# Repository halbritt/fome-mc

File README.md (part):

# `fome-mc` — Integrated FOME-Native Motorcycle ECU

**`fome-mc`** is a single-PCB, 4-layer (`162.0 mm × 115.0 mm`), pottable motorcycle engine control unit running [FOME (`fome-fw`)](https://github.com/halbritt/fome-fw) on an `STM32H753ZIT6` / `STM32H743ZIT6` paired with **two onboard `STM32F042K6T6` Bosch LSU 4.9 wideband controllers**, **four 400 V / 30 A ignition IGBTs**, **four 5 V logic ignition outputs**, **four high-Z injector drivers**, **dual 4-wire stepper drivers (`DRV8825` + `2× TLE9201SG`)**, **dual `MAX9924` adaptive VR conditioners**, **soldered 4 GB industrial SDNAND logging (`CSNP32GCR01-AOW`)**, **onboard `ATWINC1500-MR210UB` U.FL Wi-Fi**, and **dual 35-pin TE Connectivity AMPSEAL (`776163-1` Black & `776163-2` Grey) sealed harness headers**.

The primary reference application is the **2007 Suzuki SV650 (K7)** (`645 cc` 90° V-twin, odd-fire `270° / 450°`, dual spark plugs per cylinder = 4 plugs total, `24-2` crank VR trigger, camless `VVT_MAP_V_TWIN` intake-MAP phase sync, dual 4-wire steppers for `ISC` idle and `STVA` secondary throttle blades, and dual Bosch LSU 4.9 wideband O2 sensors).

---

## Documentation & Visual Index

| Document / Artifact | Description |
| :--- | :--- |
| [**`docs/WIRING_SV650_K7.md`**](docs/WIRING_SV650_K7.md) | Complete 2007 Suzuki SV650 (K7) adapter harness build guide, stock 2×34-pin ECM cavity key, mating TE AMPSEAL connector BOM, pin-by-pin `J1`/`J2` cross-reference, 2-coil vs. 4-coil Primary+Trailing ignition wiring, and dual Bosch LSU 4.9 pinouts |
| [**`docs/POTTING_AND_ENCLOSURE.md`**](docs/POTTING_AND_ENCLOSURE.md) | CNC enclosure stackup, faceplate/bulkhead cutouts, `10.44 W` continuous / `12.74 W` peak thermal dissipation budget, thermal gap-pad coupling, single-pour flood potting (external GM/Delphi 1-bar baro, `FOMEMC-1`), `U29` U.FL RF shield sealing (`FOMEMC-2`), and post-potting DFU recovery |
| [**`docs/TELEMETRY_AND_RACECHRONO.md`**](docs/TELEMETRY_AND_RACECHRONO.md) | `CAN1` motorsport telemetry pod (`ESP32-S3` + `25 Hz` GPS + `Bosch MM5.10` / `BMI088` 6-axis IMU + brake/suspension ADC), `FOME_CAN_verbose.dbc` (`0x200..0x207` @ 50 Hz), RaceChrono Pro BLE DIY integration, and Insta360 / DJI Action camera sync (`FOMEMC-4`) |
| [**`docs/DESIGN.md`**](docs/DESIGN.md) | Complete electrical architecture, circuit-block reuse/adaptation ledger, power tree, and STM32H753 resource mapping |
| [**`docs/VALIDATION.md`**](docs/VALIDATION.md) | Automated ERC/DRC/Parity/Gerber/JLCPCB DFM verification ledger and pre-engine hardware bring-up checklist |
| [**`docs/SHEET_CONTRACTS.md`**](docs/SHEET_CONTRACTS.md) | Per-sheet hierarchical pin contracts (`contracts/*.interface.json`, `633` invariants across 15 sheets / 21 instances) and cross-block coupling resolution (`FOMEMC-22`) |
| [**`docs/BLOCK_LIBRARY.md`**](docs/BLOCK_LIBRARY.md) | Reference circuit-block library capture plan and provenance inventory across `fome-mc` subsheets |
| [**`docs/SEEDED_DEFECT_BENCHMARK.md`**](docs/SEEDED_DEFECT_BENCHMARK.md) | Seeded hardware defect benchmark catalog derived from `FOMEMC-1..27` design and layout remediations |
| [**`toolchain/README.md`**](toolchain/README.md) & [**`toolchain/ROUTING.md`**](toolchain/ROUTING.md) | Reproducible KiCad 10 / `kicad-happy` / `ngspice` check runner and `kicad-route` PCB routing workflow |
| [**`docs/schematics/fome-mc-schematics.pdf`**](docs/schematics/fome-mc-schematics.pdf) | Full 21-sheet hierarchical schematic PDF (plus individual sheet SVGs in [`docs/schematics/`](docs/schematics/)) |
| [**`docs/renders/fome-mc-pcb-layers.pdf`**](docs/renders/fome-mc-pcb-layers.pdf) | Multi-page PCB layer plot PDF (`F.Cu`, `In1.Cu`, `In2.Cu`, `B.Cu`, `F.Silkscreen`, `B.Silkscreen`, `F.Fab`, `Edge.Cuts`) |
| [**3D board renderings**](docs/renders/3d/fome-mc-3d-isometric.png) | High-resolution [top](docs/renders/3d/fome-mc-3d-top.png), [bottom](docs/renders/3d/fome-mc-3d-bottom.png) and [isometric](docs/renders/3d/fome-mc-3d-isometric.png) views, with [source and model provenance](docs/renders/3d/render-manifest.json) |
| [**`io-map.csv`**](io-map.csv) | Machine-verified 92-row master pinout CSV (`J1-1..35`, `J2-1..35`, and 22 internal MCU/WBO/SDNAND/Wi-Fi/power buses) |
| [**`export/BOM-fome-mc.csv`**](export/BOM-fome-mc.csv), [**`export/CPL-fome-mc.csv`**](export/CPL-fome-mc.csv) & [**`fab-manifest.json`**](reports/toolchain/fab-manifest.json) | JLCPCB PCBA Bill of Materials (`494` populated parts across `102` lines), component placement centroids, and SHA-256 fabrication package manifest (`FOMEMC-21`, `FOMEMC-24`) |
| [**`CHANGELOG.md`**](CHANGELOG.md) | Engineering decision history, schematic/PCB integration milestones, and upstream bug fixes |

---

## System Architecture

```mermaid
flowchart TB
    subgraph J1["J1 — TE AMPSEAL 35-Pin (Black 776163-1): Power & High-Current Outputs"]
        J1_PWR["+12V_IGN_SW (J1-26)<br/>+12V_MR (J1-24, J1-27)<br/>Perm_Live (J1-28)<br/>WBO1/2_H- (J1-23, J1-25)"]
        J1_INJ["INJ1..INJ4 (J1-1..4)<br/>4x High-Z Injector LS"]
        J1_IGBT["IGBT1..IGBT4 (J1-6..9)<br/>4x 400V 30A Dumb Coil IGBTs"]
        J1_AUX["AUX_LS1..4 (J1-10..13)<br/>Fuel Pump, Fan, PAIR, Tach<br/>MAIN_RLY LS (J1-14)"]
        J1_MOT["ETB1+/- & ETB2+/- (J1-15..18)<br/>STEP_1A/1B/2A/2B (J1-19..22)"]
        J1_DFU["USB_VBUS / +12V DFU (J1-35)<br/>5V_SENSOR_1/2 (J1-29..30)<br/>Unified GND (J1-5, J1-31..34)"]
    end

    subgraph J2["J2 — TE AMPSEAL 35-Pin (Grey 776163-2): Sensors, Wideband Cells & Comms"]
        J2_ANA["CLT, IAT, TPS1, TPS2_STPS,<br/>MAP1_FRONT, AV3_BARO_MAP2,<br/>AV5_TIPOVER, AV6_GEAR (J2-1..8)"]
        J2_KNK["KNOCK1 & KNOCK2 (J2-9..10)"]
        J2_TRG["VR1+/- & VR2+/- (J2-11..14)<br/>HALL1..3 & DIN1 (J2-15..18)"]
        J2_WBO["WBO1 LSU 4.9 (J2-19..22)<br/>WBO2 LSU 4.9 (J2-30..33)"]
        J2_IGN["IGN1_LOG..IGN4_LOG (J2-23..26)<br/>DASH_TECH 7800-Baud (J2-27)"]
        J2_COM["CAN1_H/L (J2-28..29, 500 kbps)<br/>USB_D+/D- (J2-34..35)"]
    end

    subgraph PCB["fome-mc 4-Layer Integrated Motorcycle ECU PCB (162.0 mm × 115.0 mm)"]
        PSU["Power Supply & Keep-Alive (psu.kicad_sch + Keep_Alive.kicad_sch)<br/>D20/D21 B340A Diode-OR (12V_IGN_SW + 12V_MR -> 12V_RAW)<br/>SMCJ24A (D1/D22) Unidirectional TVS • AO4485 Reverse PMOS + BZT52C12<br/>L1/C6 Input Filter -> LMR16020PDDAR 60V 5V Buck • 2x TLS115D0E<br/>TLV75733PDBVR 3.3V LDO • MIC5205 VBAT (U41) • 2x MCP2551 (U4 CAN1, U5 CAN2)"]
        MCU["Main ECU Brain (sheets/mcu.kicad_sch)<br/>STM32H753ZIT6 (U26, 480 MHz Cortex-M7)<br/>CSNP32GCR01-AOW 32Gbit (4GB) SDNAND (U25, SDMMC1)<br/>ATWINC1500-MR210UB U.FL Wi-Fi (U29, SPI4 PE2..PE6 + PC13)<br/>LPS25HBTR Baro (U24 DNP, I2C2) • REF3333 Fixed 3.30V VREF+ (U23)"]
        AFE["Analog, Knock & VR Front-End<br/>MCP6004 Buffers + 2.7k 0.1% Pull-Ups<br/>2x MAX9924UAUB+ VR Conditioners (U13, U14 Mode A2)<br/>Active Bandpass Knock Filter (PF4/PF5 ADC3)"]
        DRV["Power & Motion Drivers<br/>4x MIC4427 (U42..U45 in ign1/ign2) + 4x FGD3040G2-F085 IGBTs (Q201..Q204)<br/>6x VNLD5090 Dual Low-Side (U1001..U1202) + 3x 74HCT125D (U1003..U1203) + BTS716G HS (U40)<br/>2x TLE9201SG 6A H-Bridge (U201, U203) + DRV8825 Stepper (U202)"]
        WBO["Dual Onboard LSU 4.9 Wideband Controllers<br/>WBO1 (U302 STM32F042, 0x190) & WBO2 (U402 STM32F042, 0x192)<br/>MCP6004 + AD8628 + REF3033 + VND14NV04 + TJA1051T/3 (U307/U407)<br/>Internal 500 kbps CAN2 Bus (PB12/PB13) + H7 Reset/BOOT0 (PD4..PD7)"]
    end

    J1_PWR --> PSU
    PSU --> MCU & AFE & DRV & WBO
    J2_ANA & J2_KNK & J2_TRG --> AFE --> MCU
    J2_WBO <--> WBO
    J1_PWR --> WBO
    WBO <==>|"Internal CAN2 (500 kbps)<br/>+ PD4..PD7 NRST/BOOT0"| MCU
    MCU --> DRV
    DRV --> J1_INJ & J1_IGBT & J1_AUX & J1_MOT & J2_IGN
    J2_COM & J1_DFU <--> MCU
```

---

## Hardware Capabilities at a Glance

| Subsystem | Hardware Implementation | Connectors / MCU Pins | Key Ratings & Notes |
| :--- | :--- | :--- | :--- |
| **Main MCU** | `STM32H753ZIT6` (`U26`, LQFP-144, `C730207`) | 8 MHz HSE (`Y1`, `C115962`), `REF3333AIDBZR` (`REF3033`-class) fixed `3.30 V` `VREF+` (`U23`, `C130016`) | 480 MHz Cortex-M7, 2 MB Dual-Bank Flash, 1 MB RAM. Fixed `3.30 V` `VREF+` means ADC inputs are not ratiometric to `5V_SENSOR_x`; scale by `5V_SENSE_DIVIDED` (`U26.50` / `PF12` / `EFI_ADC_17`, fed by `R118 = 10 kΩ / R119 = 10 kΩ` from `/5V_SENSOR_1`) during cranking sag |
| **Onboard Logging (`FOMEMC-3`, `FOMEMC-19`)** | `CSNP32GCR01-AOW` (`U25`, `6×8 mm` LGA-8, `C2841139`) + `C113` (`4.7 µF` `C19666`) & `C114` (`100 nF` `C161115`) `< 2.0 mm` from Pin 4 (`VDD`) | `SDMMC1` 4-bit bus (`PC8..PC12, PD2`) | 4 GB (32 Gbit) soldered pottable SD NAND (`~161 hrs` @ 50 Hz / `~80 hrs` @ 100 Hz) with automatic oldest-`.mlg` ring-buffer pruning; pin-compatible with `MKDV32GCL-STH` (`C5199868`) / `XTSD32GLGEAG` |
| **Onboard Wi-Fi (`U.FL`, `FOMEMC-2`, `FOMEMC-18`, `FOMEMC-27`)** | `ATWINC1500-MR210UB` (`U29`, `C1558703` at `(166.0, 131.5 mm, 90°)`, `14.73 × 21.72 mm` `DS70005304F` footprint + `C111 = 10 µF` `C96446` & `C112 = 10 nF` `C344025` on Pin 24 `1P3V_TP`) | `SPI4` (`PE2=SCK`, `PE5=MISO`, `PE6=MOSI`, `PE4=CS`, `PE3=IRQ`, `PC13=RST`) | Enables wireless TunerStudio TCP server (`port 29000`) and built-in HTTP port `80` web server for browsing/downloading `.mlg` logs & streaming `.zip` archives; `3.7 × 3.7 mm` `Pad 29` GND paddle with 2×2 thermal/GND vias; U.FL pigtail exits aluminum enclosure |
| **`CAN1` Motorsport Telemetry (`FOMEMC-4`)** | `MCP2551-I-SN` (`U4`, `C7376`) + `PESD1CAN-UX` (`D4`, `C907839`) + `120 Ω` (`R9`, `C22787`) + `10 Ω` (`R7`, `C22859`) | `J2-28` (`CAN1_H`), `J2-29` (`CAN1_L`), `PD1` (`FDCAN1_TX`), `PD0` (`FDCAN1_RX`) | `500 kbps` external CAN1 bus: broadcasts `FOME_CAN_verbose.dbc` (`0x200..0x207`) at **`50 Hz` (`20 ms`, `canSleepPeriodMs = 20`)** and ingests **Bosch `MM5.10` 6-axis IMU** frames (`0x174`, `0x178`, `0x17C`; RaceChrono Pro decodes all 6 axes, while FOME `can_imu.cpp` logs `YawRate` and `Accel{Lat,Lon,Vert}` into `.mlg`) |
| **Wideband O2 #1 & #2 (`FOMEMC-26`)** | `2× STM32F042K6T6` (`U302`, `U402`, `C69216`) + `2× MCP6004` (`C50282`) + `2× AD8628` (`C29309`) + `2× REF3033` (`C36658`) + `2× VND14NV04` (`Q301`, `Q401`, `C2649436`) + `2× TJA1051T/3` (`U307`, `U407`, `C38695`) | `J1-23` (`WBO1_H-`), `J1-24` (`+12V_MR`), `J1-25` (`WBO2_H-`), `J2-19..22` (`WBO1`), `J2-30..33` (`WBO2`) | Internal `CAN2` (`PB12/PB13` @ 500 kbps via `U5` `MCP2551-I-SN` to `U307/U407` `TJA1051T/3`). Strapped addresses: `WBO1` = `0x190/0x191`, `WBO2` = `0x192/0x193`. H7 controls `NRST`/`BOOT0` via `PD4..PD7`. `/WBO1_H-` (`Q301` Pad 2 -> `J1-23`) and `/WBO2_H-` (`Q401` Pad 2 -> `J1-25`) use wide (`>= 1.50 mm`) low-resistance copper buses (`<= 0.05 Ω` trace resistance/ch, `< 0.13 W` loss @ `1.6 A RMS`, `< 0.45 W` @ `3.0 A` cold-start peak) |
| **High-Current Ignition (`FOMEMC-16`, `FOMEMC-19`)** | `4× FGD3040G2-F085` IGBTs (`Q201..Q204`, TO-252, `C606124` in `/ign_igbt/`) driven by `2× MIC4427` (`U42, U43`, `C171845` in `/ign1/`) | `J1-6..9` (`PB3`, `PG15`, `PG14`, `PG13`) | `380–400 V` internal collector-gate SCIS clamp, `30 A`, `250 mJ`; dedicated `HV_IGN` netclass (`0.50 mm` min copper clearance, `1.20 mm` nominal track width across all 4 copper layers `F.Cu`, `In1.Cu`, `In2.Cu`, `B.Cu`); `10 kΩ` (`R205..R208`) gate-emitter bleeders |
| **5V Logic Ignition** | `2× MIC4427` (`U44, U45`, `C171845` in `/ign2/`) 1.5 A dual push-pull buffers + `100 Ω` (`R112..R115`, `C17408`) series protection | `J2-23..26` (`PG12`, `PG11`, `PG10`, `PG9`) | Drives 4 channels (`IGN1_LOG..IGN4_LOG` on `/IGN5../IGN8`) for 3/4-wire smart coils or external igniters; `IGBT3/4` and `IGN3/4_LOG` support independent **Trailing Spark** |
| **Fuel Injectors (`FOMEMC-13`, `FOMEMC-17`)** | `2× VNLD5090TR-E` dual protected low-side (`U1001`, `U1002`, `C222209`) + `74HCT125D` (`U1003`, `C5947`) `+5V` CMOS buffer (`D201..D204` **DNP**) | `J1-1..4` (`PG5`, `PG6`, `PG7`, `PG8`) | 4 channels (`INJ1..4`), `4.9 V` gate drive (`U1003`); `D201..D204` (`B340A-13-F`, `C64982`) marked **DNP** (`exclude_from_bom`, `dnp`) so `VNLD5090TR-E` demagnetizes high-Z injectors via its internal **`42 V` active Zener clamp** (`~0.83 ms` turn-off vs `~4.8 ms` with a `14 V` Schottky clamp, preventing nonlinear fuel delivery & AFR skew at `10,500 RPM`) |
| **Aux Low-Side, Main Relay & High-Side (`FOMEMC-13`, `FOMEMC-14`, `FOMEMC-17`, `FOMEMC-25`)** | `4× VNLD5090TR-E` (`U1101..U1202`, `C222209`) + `2× 74HCT125D` (`U1103`, `U1203`, `C5947`) `+5V` CMOS buffers + `D205..D209` (`B340A-13-F`, `C64982`) + `BTS716G` (`U40`, `C85135`, spare) | `J1-10..13` (`LS5..LS8`: `PC6, PC7, PA15, PD3`), `J1-14` (`MAIN_RLY` via `PE0` -> `U1203` -> `U1202.6` + `D209` flyback), `J2-27` (`LS14` / `DASH_TECH` via `PB9` -> `U1203` -> `U1201.8`) | `D205..D209` (`B340A-13-F`, `C64982`) populated for inductive solenoids/relays (`/LS5../LS8`, `/MAIN_RLY` on `J1-14`); `J1-13` (`/LS8` / `AUX_LS4` Tach) includes `R212 = 2.2 kΩ` (`C22976`) pull-up to `/12V_MR` (`J2-27` `DASH_TECH` is open-drain low-side; uses cluster/harness pull-up) |
| **Idle Stepper (`ISC`)** | `DRV8825PWPR` (`U202`, HTSSOP-28, `C50506`) bipolar microstepping driver | `J1-19..22` (`STEP_1A/1B/2A/2B`), `PB4` (`STEP`), `PB7` (`DIR`), `PB8` (`~EN`) | Regulated `0.77 A` chopper limit (`R213, R214 = 0.20 Ω` `1206` sense `C25335`, `VREF = 0.767 V` via `R215 = 33 kΩ` `C25779` / `R216 = 10 kΩ` `C25744` from `+3V3`) for SV650 4-wire `ISC` idle valve |
| **Secondary Throttle (`STVA`) / Dual ETB** | `2× TLE9201SG` (`U201` in `/etb1/`, `U203` inline in `/stepper_etb/`, PG-DSO-12, `C112633`) 6 A H-bridges | `J1-15..18` (`ETB1_OUT+/-`, `ETB2_OUT+/-`), `PD12/PD10/PD11` (`ETB1` `PWM/DIR/DIS`), `PD13/PD9/PD8` (`ETB2` `PWM/DIR/DIS`) | Drives SV650 4-wire `STVA` secondary throttle stepper or dual DC drive-by-wire throttles |
| **Crank/Cam VR & Hall (`FOMEMC-25`)** | `2× MAX9924UAUB+` (`U13, U14`, `LCSC C143633`) differential adaptive VR conditioners + `SN74LVC2G17DB` (`U8, U9, U10`, `C10429`) +3V3 Hall buffers + `SRV05-4` (`U11, U12`, `C85364`) ESD arrays | `J2-11..14` (`VR1+`/`VR1-` -> `PE14`, `VR2+`/`VR2-` -> `PE15`), `J2-15..18` (`DIGITAL_1..4` -> `PG1, PG0, PE11, PE10`) | Wired in **Mode A2 (Internal Adaptive Peak Threshold + Internal Bias + Zero-Crossing Watchdog Enabled)**: Pin 6 (`ZERO_EN`) = `GND`, Pin 9 (`INT_THRS`) = `GND`, Pin 4 (`BIAS`) = `GND` (`2.5 V` internal bias via `R35..R38 = 10 kΩ`), Pin 8 (`EXT`) = `NC`; `C38, C39` (`100 nF` `0603` `C161115`) `< 2 mm` from Pin 10 (`VCC = /5V_SENSOR_1`) in parallel with `C109, C110`; `R23..R28 = 2.7 kΩ` (`C13167`) pull-ups to `/5V_SENSOR_1` and `R29..R34 = 2.7 kΩ` (`C13167`) series input resistors on `DIGITAL_1..6` |
| **Analog, Baro (`FOMEMC-1`), Gear (`FOMEMC-14`), Temp & Knock** | `MCP6004` buffers (`U7, U15, U17, U19, U21`, `C50282`) + `SRV05-4` TVS arrays (`U16, U18, U20, U22`, `C85364`) | `J2-1..8` (`PC1, PC2, PA1, PA3, PA0, PA2, PA4, PA5`), `J2-9..10` (`PF4, PF5` `ADC3`) | `2.7 kΩ 0.1%` (`C13167`) bias to `/5V_SENSOR_1` on `AT1`/`AT2` (`CLT`/`IAT`); **`R219 = 1.5 kΩ 1%` (`C22843`) pull-up to `/5V_SENSOR_1` on `AV6_GEAR` (`J2-8`, `PA5`)** (`0.87–3.19 V` at `PA5` after `+5V` `U19` buffer and `5.6 kΩ / 10 kΩ` divider); **`J2-6` (`PA2` / `EFI_ADC_2`) defaults to external `MT_GM_1_BAR` (`GM 12614970` / `Delphi PS10150` `10–105 kPa`) barometer** for single-pour flood potting (`U24` `LPS25HBTR` DNP); active bandpass knock filter (`U7`) on `PF4`/`PF5` |
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
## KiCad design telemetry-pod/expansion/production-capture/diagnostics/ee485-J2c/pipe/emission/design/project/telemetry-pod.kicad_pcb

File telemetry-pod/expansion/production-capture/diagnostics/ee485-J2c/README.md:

# AGENTEE-485 J2c diagnostic: PARTIAL

The ONE diagnostic ended with 27 accepted stages, one refused stage and C1
REQUIRED_NOT_RUN; pipeline/outer exit 3. `STAGES.md` lists the actual names from
`pipeline.json.stages`. No production candidate, receipt or placement is accepted.

The emission stage saved the full schematic and annotated board, then refused
because its access-materializer child raised `ModuleNotFoundError: No module
named 'agent_ee'`. It did not produce the required 44-row reservations file. The
failure is preserved, not repaired or retried. No second emission ran.

The saved board hash is
`fec5170a497bfad0d56be7e12c8d2597fe4541a0ed2c1bb60c3980933a6704c9`.
`j2-verification/native-checks.json` is explicitly PARTIAL: independent checks
completed before the strict verifier refused the absent access evidence. It
records the complete J2 UUID, electrical membership, stock pad/drill/layer parity,
front (80,28) pose, source-to-native RF mappings and every prohibition, source
component/ref/pad/net identities, and native BOM/CPL consumer results.

The source has 314 intent components, including five symbol-only power flags.
All 309 electrical footprints and four envelope-defined board-only mounting
holes are accounted for: 313 native footprints, with no numerical substitution
or inventory waiver. All 1,059 electrical-footprint pads are enumerated. The
source has 182 nets and 53 no-connect declarations; 886 connected terminals were
checked. BOM/CPL evidence has 93 grouped BOM rows and 296 CPL rows. J1 and J2
remain populated and carry `JLCPCB_Assembly=not_assembled`; the full native
identity comparison retains 80 LCSC identities and external Amphenol 132134.

Native tool execution passed using the repository ERC/DRC adapters on an isolated
snapshot. ERC: one sheet, zero violations. DRC: 15 violations, 499 unconnected
items, zero schematic-parity errors. The violations are one L1/L2 courtyard
overlap, 12 text-height/thickness warnings and two J1/J3 library-footprint
warnings. Nothing is waived. The text limits are existing KiCad project settings
without a cited manufacturer source in the captured fab profile: class: default,
advisory; they are not new acceptance gates. This is an unrouted diagnostic,
with no physical access, functional placement, return-path or manufacturing
acceptance.

The full native candidate is under `pipe/emission/design`; the frozen source
capture is under `cap`. `native/` holds native reports and source hashes.
Receipt JSONs under `receipt-metadata/` are metadata only, not accepted receipts.
No runtime observation/receipt write followed the refusing pipeline.

## Source boundary

The emission archive is exactly fome-mc `3db711151c1c98edbe598f72f9a77d116eaf9f32`.
The remaining prefix-only UUID guard in pipeline.py was discovered after that
archive began running. The delivered caller uses the same complete-UUID helper
as the verifier; the frozen run was not edited. The final candidate independently
passes that complete-UUID check, including the prior same-prefix negative control.
This final caller change was not exercised by another full emission.

The verifier was subsequently corrected to account for the envelope's four
board-only mounting holes and to retain successful independent checks before
refusing missing access evidence. The first inventory refusal and the subsequent
strict missing-access refusal are both retained. These are verifier-contract
corrections on the same unchanged saved bytes, not new emissions.

## Validation

Commands ran from the assigned worktree on proximal; all tests/native gates used
admission. `validation/ee485.mk` and the retained drivers contain exact recipes.
Logs preserve failures as well as final outcomes.

- Bootstrap: wrapper exit 0, `fome-bootstrap: OK`; only the permitted host apt
  patch drift. Container doctor: PASS, 54 checks, zero required failures.
- `fome-gate.sh "$WT" ... doctor check MAKEFILES=build/ee485.mk`: all five ECU
  steps PASS, exit 0. `ecu-before-after.json` proves identical before/after gate
  results and 94 byte-unchanged snapshot source files.
- Six retention tests; eight native UUID/RF tests; 19 launch-preflight tests:
  final logs end OK / exit 0. Five saved-inventory negative controls: OK / exit 0.
- Retention check: 428 retained files, 576 design inputs, eight installed files,
  4,336 prepared files. Exact materialization: 4,336 files and 108 empty dirs.
  The separate immutable repair store has 570 blobs plus index/checksums.
- Merged F8 `SHA256SUMS`: every entry OK, exit 0. Main's F8 manifest and correction
  record, historical retention and historical J2 import remain byte unchanged.
- Final `build.py /work/export --check`: byte-for-byte reproduction, exit 0.
- ONE emission: test/1, three CPUs, 12 GiB, 1,800-second cap, jobs 1; selected
  runtime `agentee-485j2c.json`, exact mounted agent-ee 00d3243a, C1 held.
- `python3 verify_j2.py <run>`: strict refusal, Python exit 1 / make exit 2,
  missing `pipe/access-rebound/reservations.json`; successful native checks are
  explicitly partial. Native ERC/DRC and position-export tools exit 0.

No routing/campaign launch, receipt acceptance, rule relaxation, purchase, vendor
upload, tracker/main change or additional agent was performed. Hosted CI is
NOT EVIDENCE (not observed, not required). Model route: Sol (Codex), HIGH as
dispatched; exact runtime model identifier is not exposed by the harness.

The first seal's overbroad whitespace check inspected captured PDF bytes and
reported trailing whitespace. Those bytes remain unchanged. The final whitespace
check excludes the hash-bound `cap/`, emitted `design/` and raw `logs/` trees;
`SHA256SUMS` still verifies every retained file. Human-authored code and notes
remain covered by whitespace checks.

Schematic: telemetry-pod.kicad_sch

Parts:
C1, C2, C8, C9: 4.7 uF/100 V; C_1210_3225Metric; Voltage 100V; Partnumber CL32B475KCVZNWE; LCSC C17288249
C3, C10: 220 nF/100 V; C_0805_2012Metric; Voltage 100V; Partnumber CL21B224KCFSFNE; LCSC C307542
C4, C11, C16, C20, C21, C22, C44, C130: 1 uF/16 V; C_0603_1608Metric; Voltage 16V; Partnumber CGA3E1X7R1C105KT0Y0N; LCSC C76706
C5, C12, C30, C32, C34, C36, C38, C39, C41, C42, C43, C54, C56, C58, C60, C131, C132, C133: 100 nF/50 V X7R; C_0603_1608Metric; Voltage 50V; Partnumber CGA3E2X7R1H104KT0Y0N; LCSC C76711
C6, C7, C13, C14, C15, C17, C18, C19: 22 uF/25 V; C_1210_3225Metric; Voltage 25V; Partnumber CGA6P3X7R1E226MT000N; LCSC C694521
C31, C33, C35, C37, C55, C57, C59, C61: 100 pF C0G/50 V; C_0603_1608Metric; Voltage 50V; Partnumber C0603C101J5GACTU; LCSC C2167328
C40: 470 pF C0G/50 V; C_0603_1608Metric; Voltage 50V; Partnumber C0603C471J5GACTU; LCSC C452751
C45: 22uF; C_1210_3225Metric; Voltage 25V; Partnumber CGA6P3X7R1E226MT000N; LCSC C694521
C46, C48, C49, C51, C53, C62: 100nF; C_0603_1608Metric; Voltage 50V; Partnumber CGA3E2X7R1H104KT0Y0N; LCSC C76711
C47: 10nF; C_0603_1608Metric; Voltage 50V; Partnumber GRM1885C1H103JA01D; LCSC C85973
C50, C52: 1uF; C_0603_1608Metric; Voltage 16V; Partnumber CGA3E1X7R1C105KT0Y0N; LCSC C76706
C64: 4.7 uF/16 V X7R; C_0805_2012Metric; Voltage 16V; Partnumber C0805C475K4RACTU; LCSC C7224519
C65, C72, C76, C78, C79, C83, C84, C85: 100nF; C_0603_1608Metric; Voltage 50V; Partnumber C0603C104K5RACTU; LCSC C127833
C71, C75, C77: 22nF; C_0603_1608Metric; Voltage 50V; Partnumber C0603C223K5RACTU; LCSC C2167136
C80: 1uF; C_0603_1608Metric; Voltage 16V; Partnumber C0603C105K4RACTU; LCSC C2167386
C81, C82: 18pF C0G; C_0603_1608Metric; Voltage 50V; Partnumber C0603C180J5GACTU; LCSC C2168350
C86, C89, C92, C98, C118, C119, C120, C121, C122, C123, C124: 1uF 50V X7R; C_0805_2012Metric; Voltage 50V; Partnumber C0805C105K5RACTU; LCSC C3018567
C87, C90, C93, C97, C110, C111, C112, C114, C115, C116, C117, C125, C127, C129: 100nF 50V X7R; C_0603_1608Metric; Voltage 50V; Partnumber C0603C104K5RACTU; LCSC C127833
C88, C91, C94, C126: 10nF 50V C0G 10%; C_0603_1608Metric; Voltage 50V; Partnumber GRM1885C1H103JA01D; LCSC C85973
C95, C96: 220pF C0G; C_0603_1608Metric; Voltage 50V; Partnumber C0603C221J5GACTU; LCSC C452747
C100: 100n; C_0402_1005Metric; Voltage 16V; Partnumber CL05B104KO5NNNC; LCSC C1525
C128: 10uF 16V X7R; C_1206_3216Metric; Voltage 16V; Partnumber C1206C106K4RACTU; LCSC C2174822
D1: SMCJ24CA; D_SMC; Partnumber SMCJ24CA; LCSC C151279
D2: BZT52C12-7-F; D_SOD-123; Partnumber BZT52C12-7-F; LCSC C124196
D3: PESD5V0C1BLS-QYL; SOD882BD; Partnumber PESD5V0C1BLS-QYL; LCSC C5311564
D100: PESD1CAN-UX; SOT-323_SC-70; Partnumber PESD1CAN-UX; LCSC C907839
D101, D104: PESD2CANFD24V-TR; SOT-23; Partnumber PESD2CANFD24V-TR; LCSC C552486
D102, D103, D105: BAV199,215; SOT-23; Partnumber BAV199,215; LCSC C40919
J1: 1-776163-1; AMPSEAL_35_1-776163-1; Partnumber 1-776163-1; JLCPCB_Assembly not_assembled
J2: 132134; SMA_Amphenol_132134_Manufacturer; Partnumber 132134; JLCPCB_Assembly not_assembled
J3: DM3AT-SF-PEJM5; microSD_HC_Hirose_DM3AT-SF-PEJM5; Partnumber DM3AT-SF-PEJM5; LCSC C114218
JP1: TIRE_TERM_CLOSE_ONLY_AT_BUS_END; SolderJumper-2_P1.3mm_Open_RoundedPad1.0x1.5mm
JP2: AUX1_THERM_PULLUP_CLOSE_TO_ENABLE; SolderJumper-2_P1.3mm_Open_RoundedPad1.0x1.5mm
JP3: AUX2_THERM_PULLUP_CLOSE_TO_ENABLE; SolderJumper-2_P1.3mm_Open_RoundedPad1.0x1.5mm
JP4: AUX3_THERM_PULLUP_CLOSE_TO_ENABLE; SolderJumper-2_P1.3mm_Open_RoundedPad1.0x1.5mm
JP5: AUX4_THERM_PULLUP_CLOSE_TO_ENABLE; SolderJumper-2_P1.3mm_Open_RoundedPad1.0x1.5mm
L1: 15 uH; SRP7050TA; Partnumber SRP7050TA-150M; LCSC C2045384
L2: 6.8 uH; SRP7050WA; Partnumber SRP7050WA-6R8M; LCSC C19947708
L3: LQW18AN56NJ00D; L_0603_1608Metric; Partnumber LQW18AN56NJ00D; LCSC C98080
Q1: DMP6023LE-13; DMP6023LE_SOT223; Partnumber DMP6023LE-13; LCSC C154901
R1, R24, R25: 100 kohm; R_0603_1608Metric; Partnumber RC0603FR-07100KL; LCSC C14675
R2: 51 kohm; R_0603_1608Metric; Partnumber RT0603BRD0751KL; LCSC C861458
R3, R5, R10, R11, R13, R14, R16, R17, R19, R20, R22, R23, R34, R35, R37, R38, R40, R41, R43, R44, R46, R47, R48, R49, R50, R55, R64, R65, R66, R67, R68, R69, R71, R72: 10 kohm; R_0603_1608Metric; Partnumber RT0603BRD0710KL; LCSC C95204
R4: 22 kohm; R_0603_1608Metric; Partnumber RT0603BRD0722KL; LCSC C469656
R6: 47 kohm; R_0603_1608Metric; Partnumber RC0603FR-0747KL; LCSC C105579
R7: 1 ohm; R_0603_1608Metric; Partnumber RC0603FR-071RL; LCSC C112305
R12, R15, R18, R21, R36, R39, R42, R45: 100 ohm; R_0603_1608Metric; Partnumber RC0603FR-07100RL; LCSC C105588
R26: 10 ohm/0.25 W; R_1206_3216Metric; Partnumber RC1206FR-0710RL; LCSC C108080
R27: 2 kohm; R_0603_1608Metric; Partnumber RT0603BRD072KL; LCSC C728588
R28: 1 kohm; R_0603_1608Metric; Partnumber RT0603BRD071KL; LCSC C110776
R29: 100 kohm; R_0603_1608Metric; Partnumber RT0603BRD07100KL; LCSC C122538
R30, R31, R32, R33: 10k; R_0603_1608Metric; Partnumber RT0603BRD0710KL; LCSC C95204
R56: 16.9 kohm 0.1%; R_0603_1608Metric; Partnumber RT0603BRD0716K9L; LCSC C861156
R57, R61, R63, R112, R113, R115, R121, R122, R124: 10 kohm 0.1%; R_0603_1608Metric; Partnumber RT0603BRD0710KL; LCSC C95204
R60: 30.1 kohm 0.1% 25ppm/K; R_0603_1608Metric; Partnumber RT0603BRD0730K1L; LCSC C705764
R62: 64.9 kohm 0.1%; R_0603_1608Metric; Partnumber RT0603BRD0764K9L; LCSC C861510
R70: 120 ohm; R_0603_1608Metric; Partnumber RT0603BRD07120RL; LCSC C861094
R73, R77, R81, R162: 1.05 Mohm 0.1% 25ppm/K; R_0805_2012Metric; Partnumber RT0805BRD071M05L; LCSC C7353633
R74, R78, R82: 75 kohm 0.1% 25ppm/K; R_0603_1608Metric; Partnumber RT0603BRD0775KL; LCSC C723587
R75, R79, R83: 208 kohm 0.1% 25ppm/K; R_0603_1608Metric; Partnumber RT0603BRD07208KL; LCSC C861219
R76, R80: 44.2 kohm 0.1%; R_0603_1608Metric; Partnumber RT0603BRD0744K2L; LCSC C861410
R84: 26.7 kohm 0.1%; R_0603_1608Metric; Partnumber RT0603BRD0726K7L; LCSC C728587
R100: 120; R_0603_1608Metric; Partnumber 0603WAF1200T5E; LCSC C22787
R110, R111, R119, R120: 620 ohm; R_2512_6332Metric; Partnumber CRCW2512620RFKEG; LCSC C3988368
R114, R123: 56 kohm 0.1%; R_0603_1608Metric; Partnumber RT0603BRD0756KL; LCSC C705785
R116, R125: 100 kohm 0.1%; R_0603_1608Metric; Partnumber RT0603BRD07100KL; LCSC C122538
R117, R126: 4.7 kohm 1%; R_0603_1608Metric; Partnumber RT0603BRD074K7L; LCSC C513565
R118, R127: 100 ohm; R_0603_1608Metric; Partnumber RT0603BRD07100RL; LCSC C122970
R128, R129, R130, R132, R133, R134, R136, R137, R138, R144, R145, R146, R148, R149, R150, R152, R153, R154, R156, R157, R158, R166, R167, R168: 499 kohm 0.1% 25ppm/C; R_0603_1608Metric; Partnumber RT0603BRD07499KL; LCSC C515607
R131, R135, R139, R147, R151, R155, R159, R169: 4.99 kohm 0.1% 25ppm/C; R_0603_1608Metric; Partnumber RT0603BRD074K99L; LCSC C723532
R160, R161: 2.2 kohm 1% 100ppm/C; R_0603_1608Metric; Partnumber RT0603BRD072K2L; LCSC C861295
R163: 95.3 kohm 0.1% 25ppm/K; R_0603_1608Metric; Partnumber RT0603BRD0795K3L; LCSC C861605
R164: 287 kohm 0.1% 25ppm/K; R_0603_1608Metric; Partnumber RT0603BRD07287KL; LCSC C861279
R165: 44.2 kohm 0.1% 25ppm/K; R_0603_1608Metric; Partnumber RT0603BRD0744K2L; LCSC C861410
R170, R171, R172, R173: 10 kohm 0.1% 25ppm/K; R_0603_1608Metric; Partnumber RT0603BRD0710KL; LCSC C95204
R174, R175: 200 ohm 1% 100ppm/K 1.5W CRCW2512-HP; R_2512_6332Metric; Partnumber CRCW2512200RFKEGHP; LCSC C2073505
R176, R177, R178: 499 kohm 0.1% 25ppm/K; R_0603_1608Metric; Partnumber RT0603BRD07499KL; LCSC C515607
R179: 4.99 kohm 0.1% 25ppm/K; R_0603_1608Metric; Partnumber RT0603BRD074K99L; LCSC C723532
R180: 100 kohm 1% 100ppm/K; R_0603_1608Metric; Partnumber RT0603BRD07100KL; LCSC C122538
R181: 1.2 kohm 0.1% 25ppm/K; R_0603_1608Metric; Partnumber RT0603BRD071K2L; LCSC C136970
TP1: POD_UART_TX; PogoPad_D1.5mm
TP2: POD_UART_RX; PogoPad_D1.5mm
TP3: GND; PogoPad_D1.5mm
TP4: MCU_EN; PogoPad_D1.5mm
TP5: MCU_BOOT; PogoPad_D1.5mm
TP6: +3V3; PogoPad_D1.5mm
U1: ESP32-S3-WROOM-1-N8; ESP32-S3-WROOM-1; Partnumber ESP32-S3-WROOM-1-N8; LCSC C2913198
U2: LSM6DSO32TR; LGA-14_3x2.5mm_P0.5mm_LayoutBorder3x4y; Partnumber LSM6DSO32TR; LCSC C1864162
U3: NEO-M9N-00B; ublox_NEO; Partnumber NEO-M9N-00B; LCSC C5119087
U4: MCP3208-BI/SL; SOIC-16_3.9x9.9mm_P1.27mm; Partnumber MCP3208-BI/SL; LCSC C2979740
U5, U7: LMR36520ADDAR; DDA0008B; Partnumber LMR36520ADDAR; LCSC C2879422
U6, U12: TPS7B4253QDDARQ1; DDA0008J_C02; Partnumber TPS7B4253QDDARQ1; LCSC C129339
U8, U13: ADA4096-4ARUZ-R7; TSSOP-14_4.4x5mm_P0.65mm; Partnumber ADA4096-4ARUZ-R7; LCSC C208539
U9: OPA320AIDBVR; SOT-23-5; Partnumber OPA320AIDBVR; LCSC C92494
U10: TPS2553QDBVRQ1; SOT-23-6; Partnumber TPS2553QDBVRQ1; LCSC C130055
U11: REF5050AIDR; SOIC-8_3.9x4.9mm_P1.27mm; Partnumber REF5050AIDR; LCSC C27804
U16, U18, U19: TPS389001DSER; DSE0006A; Partnumber TPS389001DSER; LCSC C1509297
U20: MCP2518FDT-E/SL; SOIC-14_3.9x8.7mm_P1.27mm; Partnumber MCP2518FDT-E/SL; LCSC C626758
U21: TJA1051T/3/1J; SOIC-8_3.9x4.9mm_P1.27mm; Partnumber TJA1051T/3/1J; LCSC C38695
U22: SN74LVC1G132DBVR; SOT-23-5; Partnumber SN74LVC1G132DBVR; LCSC C403723
U23, U24, U25, U30: TPS26625DRCR; VSON-10-1EP_3x3mm_P0.5mm_EP1.65x2.4mm; Partnumber TPS26625DRCR; LCSC C2862873
U26: LM2903BQDRQ1; SOIC-8_3.9x4.9mm_P1.27mm; Partnumber LM2903BQDRQ1; LCSC C3659057
U27, U28, U29: ADS1119IPWR; TSSOP-16_4.4x5mm_P0.65mm; Partnumber ADS1119IPWR; LCSC C701613
U31: TL431BQDBZR; SOT-23; Partnumber TL431BQDBZR; LCSC C190245
U100: TJA1051T-3; SOIC-8_3.9x4.9mm_P1.27mm; Partnumber TJA1051T/3/1J; LCSC C38695
Y1: X1E0003410031 20MHz 12pF; Crystal_SMD_SeikoEpson_FA238-4Pin_3.2x2.5mm; Partnumber X1E0003410031; LCSC C725712

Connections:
/+3V3: C13.1, C14.1, C15.1, C38.1, C41.1, C43.1, C44.1, C45.1, C46.1, C48.1, C49.1, C50.1, C51.1, C52.1, C53.1, C62.1, C64.1, C65.1, C72.1, C76.1, C78.1, C79.1, C80.1, C84.1, C85.1, C118.1, C119.1, C120.1, C121.1, C122.1, C123.1, C130.1, C131.1, C132.1, C133.1, J3.4 (VDD), L2.2, R4.1, R25.2, R29.1, R30.1, R31.1, R32.1, R46.1, R47.1, R48.1, R49.1, R50.1, R55.2, R56.1, R64.1, R65.1, R66.1, R67.1, R69.1, R71.1, R114.1, R117.1, R123.1, R126.1, R136.1, R160.1, R161.1, TP6.1, U1.2 (3V3), U2.5 (VDDIO), U2.8 (VDD), U3.2 (D_SEL), U3.22 (V_BCKP), U3.23 (VCC), U4.16 (Vdd), U8.4 (V+), U9.5 (V+), U10.1 (IN), U10.5 (ILIM), U13.4 (V+), U16.3 (MR), U16.4 (VDD), U18.3 (MR), U18.4 (VDD)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
/+5V_CAN: C19.1, C83.1, C84.2, C100.1, C133.2, U12.1 (OUT), U12.4 (FB), U21.3 (VCC), U100.3 (VCC)
/ADC_AIN0: C31.1, R12.2, U4.1 (CH0)
/ADC_AIN1: C33.1, R15.2, U4.2 (CH1)
/ADC_AIN2: C35.1, R18.2, U4.3 (CH2)
/ADC_AIN3: C37.1, R21.2, U4.4 (CH3)
/ADC_AIN4: C55.1, R36.2, U4.5 (CH4)
/ADC_AIN5: C57.1, R39.2, U4.6 (CH5)
/ADC_AIN6: C59.1, R42.2, U4.7 (CH6)
/ADC_AIN7: C61.1, R45.2, U4.8 (CH7)
/ADC_CS: R32.2, U1.17 (IO9), U4.10 (~CS/SHDN)
/AFE_BUF0: R12.1, U8.1 (OUTA), U8.2 (-INA)
/AFE_BUF1: R15.1, U8.6 (-INB), U8.7 (OUTB)
/AFE_BUF2: R18.1, U8.8 (OUTC), U8.9 (-INC)
/AFE_BUF3: R21.1, U8.13 (-IND), U8.14 (OUTD)
/AFE_BUF4: R36.1, U13.1 (OUTA), U13.2 (-INA)
/AFE_BUF5: R39.1, U13.6 (-INB), U13.7 (OUTB)
/AFE_BUF6: R42.1, U13.8 (OUTC), U13.9 (-INC)
/AFE_BUF7: R45.1, U13.13 (-IND), U13.14 (OUTD)
/AFE_DIV0: C30.1, R10.2, R11.1, U8.3 (+INA)
/AFE_DIV1: C32.1, R13.2, R14.1, U8.5 (+INB)
/AFE_DIV2: C34.1, R16.2, R17.1, U8.10 (+INC)
/AFE_DIV3: C36.1, R19.2, R20.1, U8.12 (+IND)
/AFE_DIV4: C54.1, R34.2, R35.1, U13.3 (+INA)
/AFE_DIV5: C56.1, R37.2, R38.1, U13.5 (+INB)
/AFE_DIV6: C58.1, R40.2, R41.1, U13.10 (+INC)
/AFE_DIV7: C60.1, R43.2, R44.1, U13.12 (+IND)
/ANT_BIAS: C42.1, L3.1, R26.2
/ANT_LIMITED: R26.1, U10.6 (OUT)
/BOOT_3V3: C12.1, U7.7 (BOOT)
/BOOT_PRE: C5.1, U5.7 (BOOT)
/DIAG_I2C_SCL: R161.2, U1.23 (IO21), U27.16 (SCL), U28.16 (SCL), U29.16 (SCL)
/DIAG_I2C_SDA: R160.2, U1.22 (IO14), U27.15 (SDA), U28.15 (SDA), U29.15 (SDA)
/DIAG_U27_AIN0: C110.1, R130.2, R131.1, U27.11 (AIN0)
/DIAG_U27_AIN0_UPPER1: R128.2, R129.1
/DIAG_U27_AIN0_UPPER2: R129.2, R130.1
/DIAG_U27_AIN1: C111.1, R134.2, R135.1, U27.10 (AIN1)
/DIAG_U27_AIN1_UPPER1: R132.2, R133.1
/DIAG_U27_AIN1_UPPER2: R133.2, R134.1
/DIAG_U27_AIN2: C112.1, R138.2, R139.1, U27.7 (AIN2)
/DIAG_U27_AIN2_UPPER1: R136.2, R137.1
/DIAG_U27_AIN2_UPPER2: R137.2, R138.1
/DIAG_U28_AIN1: C114.1, R146.2, R147.1, U28.10 (AIN1)
/DIAG_U28_AIN1_UPPER1: R144.2, R145.1
/DIAG_U28_AIN1_UPPER2: R145.2, R146.1
/DIAG_U28_AIN2: C127.1, R168.2, R169.1, U28.7 (AIN2)
/DIAG_U28_AIN2_UPPER1: R166.2, R167.1
/DIAG_U28_AIN2_UPPER2: R167.2, R168.1
/DIAG_U28_AIN3: C129.1, R178.2, R179.1, U28.6 (AIN3)
/DIAG_U28_AIN3_UPPER1: R176.2, R177.1
/DIAG_U28_AIN3_UPPER2: R177.2, R178.1
/DIAG_U29_AIN0: C115.1, R150.2, R151.1, U29.11 (AIN0)
/DIAG_U29_AIN0_UPPER1: R148.2, R149.1
/DIAG_U29_AIN0_UPPER2: R149.2, R150.1
/DIAG_U29_AIN1: C116.1, R154.2, R155.1, U29.10 (AIN1)
/DIAG_U29_AIN1_UPPER1: R152.2, R153.1
/DIAG_U29_AIN1_UPPER2: R153.2, R154.1
/DIAG_U29_AIN2: C117.1, R158.2, R159.1, U29.7 (AIN2)
/DIAG_U29_AIN2_UPPER1: R156.2, R157.1
/DIAG_U29_AIN2_UPPER2: R157.2, R158.1
/FB_3V3: R5.1, R28.2, U7.5 (FB)
/FB_3V3_SERIES: R4.2, R28.1
/FB_PRE: R3.1, R27.2, U5.5 (FB)
/FB_PRE_SERIES: R2.2, R27.1
/GND: C1.2, C2.2, C3.2, C4.2, C6.2, C7.2, C8.2, C9.2, C10.2, C11.2, C13.2, C14.2, C15.2, C16.2, C17.2, C18.2, C19.2, C20.2, C21.2, C22.2, C30.2, C31.2, C32.2, C33.2, C34.2, C35.2, C36.2, C37.2, C38.2, C39.2, C40.2, C41.2, C42.2, C43.2, C44.2, C45.2, C46.2, C47.2, C48.2, C49.2, C50.2, C51.2, C52.2, C53.2, C54.2, C55.2, C56.2, C57.2, C58.2, C59.2, C60.2, C61.2, C62.2, C64.2, C65.2, C71.2, C72.2, C75.2, C76.2, C77.2, C78.2, C79.2, C80.2, C81.2, C82.2, C83.2, C85.2, C86.2, C87.2, C89.2, C90.2, C92.2, C93.2, C95.2, C96.2, C97.2, C98.2, C100.2, C110.2, C111.2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
/GNSS_ANT_FAULT_N: R25.1, U10.4 (FAULT)
/GNSS_LNA_EN: R24.1, U3.14 (LNA_EN), U10.3 (EN)
/GNSS_PPS: U1.7 (IO7), U3.3 (TIMEPULSE)
/GNSS_RX_IN: U1.10 (IO17), U3.21 (RXD/SPI_MOSI)
/GNSS_TX_OUT: U1.11 (IO18), U3.20 (TXD/SPI_MISO)
/IMU_CS: R31.2, U1.18 (IO10), U2.12 (CS)
/IMU_INT1: U1.6 (IO6), U2.4 (INT1)
/MCU_BOOT: R30.2, TP5.1, U1.27 (IO0)
/MCU_BOOT46: R33.1, U1.16 (IO46)
/MCU_EN: C47.1, R29.2, TP4.1, U1.3 (EN), U16.6 (RESET), U22.1 (A)
/POD_5V_AUX: C125.1, D105.1 (A1), J1.21, R166.1, R180.1, U30.10 (OUT)
/POD_5V_SENSOR: C17.1, C124.1, J1.5, J1.8, J1.11, J1.14, R6.1, R22.1, R60.1, R144.1, R162.1, U6.1 (OUT), U6.4 (FB), U30.1 (IN)
/POD_12V_IN: D1.1 (A1), J1.3, Q1.2 (D)
/POD_12V_PROTECTED: C1.1, C2.1, C3.1, C8.1, C9.1, C10.1, D2.1 (K), Q1.3 (S), R62.1, R128.1, U5.2 (VIN), U5.3 (EN), U7.2 (VIN), U7.3 (EN)
/POD_AUX1_SIGNAL: J1.17, JP2.2 (B), R34.1
/POD_AUX2_SIGNAL: J1.18, JP3.2 (B), R37.1
/POD_AUX3_SIGNAL: J1.19, JP4.2 (B), R40.1
/POD_AUX4_SIGNAL: J1.20, JP5.2 (B), R43.1
/POD_CAN_N: D100.1 (A1), J1.2, R100.2, U100.6 (CANL)
/POD_CAN_P: D100.2 (A2), J1.1, R100.1, U100.7 (CANH)
/POD_FRONT_BRAKE_SIGNAL: J1.12, R16.1
/POD_FRONT_FORK_SIGNAL: J1.6, R10.1
/POD_GNSS_RF: D3.1 (A1), J2.1 (In), L3.2, U3.11 (RF_IN)
/POD_REAR_BRAKE_SIGNAL: J1.15, R19.1
/POD_REAR_SHOCK_SIGNAL: J1.9, R13.1
/POD_TIRE_SUPPLY: C93.1, J1.31, R156.1, U25.10 (OUT)
/POD_UART_RX: TP2.1, U1.36 (RXD0)
/POD_UART_TX: TP1.1, U1.37 (TXD0)
/POD_WHEEL_FRONT_SIGNAL: D102.3 (K1_A2), D104.1 (K1), J1.24
/POD_WHEEL_FRONT_SUPPLY: C87.1, J1.23, R110.1, R148.1, U23.10 (OUT)
/POD_WHEEL_REAR_SIGNAL: D103.3 (K1_A2), D104.2 (K2), J1.27
/POD_WHEEL_REAR_SUPPLY: C90.1, J1.26, R119.1, R152.1, U24.10 (OUT)
/POWER_FAIL_N: R65.2, U1.12 (IO8), U19.6 (RESET)
/PRE_6V3: C6.1, C7.1, C16.1, C18.1, C20.1, C86.1, C89.1, C92.1, C97.1, C98.1, L1.2, R2.1, R73.1, R77.1, R81.1, R132.1, U6.8 (IN), U11.2 (Vin), U12.8 (IN), U23.1 (IN), U24.1 (IN), U25.1 (IN), U26.8 (VCC)
/REF_CAP_NODE: C22.1, R7.2
/REF_DIV: C39.1, R22.2, R23.1, U9.3 (+IN)
/REF_NR: C21.1, U11.5 (Trim/NR)
/REVERSE_GATE: D2.2 (A), Q1.1 (G), R1.1
/SD_CD: J3.9 (DET_B), R55.1, U1.28 (IO35)
/SD_CLK: J3.5 (CLK), U1.31 (IO38)
/SD_CMD: J3.3 (CMD), R46.2, U1.32 (IO39)
/SD_DAT0: J3.7 (DAT0), R47.2, U1.33 (IO40)
/SD_DAT1: J3.8 (DAT1), R48.2, U1.34 (IO41)
/SD_DAT2: J3.1 (DAT2), R49.2, U1.35 (IO42)
/SD_DAT3: J3.2 (DAT3/CD), R50.2, U1.24 (IO47)
/SENSOR_FAULT_N: R64.2, U1.25 (IO48), U18.6 (RESET)
/SENSOR_POWER_AUX_DVDT: C126.1, U30.8 (dVdT)
/SENSOR_POWER_AUX_ILIM: R165.1, U30.7 (ILIM)
/SENSOR_POWER_AUX_OVP: R163.2, R164.1, U30.3 (OVP)
/SENSOR_POWER_AUX_RTN: C126.2, R164.2, R165.2, U30.5 (RTN), U30.11 (EP_RTN)
/SENSOR_POWER_AUX_UVLO: R162.2, R163.1, U30.2 (UVLO)
/SENSOR_POWER_FRONT_DVDT: C88.1, U23.8 (dVdT)
/SENSOR_POWER_FRONT_ILIM: R76.1, U23.7 (ILIM)
/SENSOR_POWER_FRONT_OVP: R74.2, R75.1, U23.3 (OVP)
/SENSOR_POWER_FRONT_RTN: C88.2, R75.2, R76.2, U23.5 (RTN), U23.11 (EP_RTN)
/SENSOR_POWER_FRONT_UVLO: R73.2, R74.1, U23.2 (UVLO)
/SENSOR_POWER_REAR_DVDT: C91.1, U24.8 (dVdT)
/SENSOR_POWER_REAR_ILIM: R80.1, U24.7 (ILIM)
/SENSOR_POWER_REAR_OVP: R78.2, R79.1, U24.3 (OVP)
/SENSOR_POWER_REAR_RTN: C91.2, R79.2, R80.2, U24.5 (RTN), U24.11 (EP_RTN)
/SENSOR_POWER_REAR_UVLO: R77.2, R78.1, U24.2 (UVLO)
/SENSOR_POWER_TIRE_DVDT: C94.1, U25.8 (dVdT)
/SENSOR_POWER_TIRE_ILIM: R84.1, U25.7 (ILIM)
/SENSOR_POWER_TIRE_OVP: R82.2, R83.1, U25.3 (OVP)
/SENSOR_POWER_TIRE_RTN: C94.2, R83.2, R84.2, U25.5 (RTN), U25.11 (EP_RTN)
/SENSOR_POWER_TIRE_UVLO: R81.2, R82.1, U25.2 (UVLO)
/SENSOR_REF_2V5: C40.1, U4.15 (Vref), U9.1 (OUT), U9.4 (-IN)
/SETPOINT_5V: R7.1, U6.5 (ADJ), U11.6 (Vout), U12.5 (ADJ)
/SPI_MISO: U1.21 (IO13), U2.1 (SDO), U4.12 (Dout), U20.12 (SDO)
/SPI_MOSI: U1.19 (IO11), U2.14 (SDA), U4.11 (Din), U20.11 (SDI)
/SPI_SCK: U1.20 (IO12), U2.13 (SCL), U4.13 (CLK), U20.10 (SCK)
/SUP_U16_CT: C71.1, U16.5 (CT)
/SUP_U16_SENSE: R56.2, R57.1, U16.1 (SENSE)
/SUP_U18_CT: C75.1, U18.5 (CT)
/SUP_U18_SENSE: R61.1, R181.2, U18.1 (SENSE)
/SUP_U18_TOP_SERIES: R60.2, R181.1
/SUP_U19_CT: C77.1, U19.5 (CT)
/SUP_U19_SENSE: R62.2, R63.1, U19.1 (SENSE)
/SW_3V3: C12.2, L2.1, U7.8 (SW)
/SW_PRE: C5.2, L1.1, U5.8 (SW)
/THERM_AUX1_SELECT: JP2.1 (A), R170.2
/THERM_AUX2_SELECT: JP3.1 (A), R171.2
/THERM_AUX3_SELECT: JP4.1 (A), R172.2
/THERM_AUX4_SELECT: JP5.1 (A), R173.2
/THERM_BIAS_IN: D105.3 (K1_A2), R174.1
/THERM_BIAS_MID: R174.2, R175.1
/THERM_EXC_2V495: C128.1, R170.1, R171.1, R172.1, R173.1, R175.2, R176.1, U31.1 (K), U31.2 (REF)
/TIRE_CAN_CS: R66.2, U1.8 (IO15), U20.13 (nCS)
/TIRE_CAN_GPIO1: R72.1, U20.8 (GPIO1)
/TIRE_CAN_H: D101.1 (K1), J1.29, J1.33, R70.1, U21.7 (CANH)
/TIRE_CAN_INT_N: R67.2, U1.9 (IO16), U20.4 (INT)
/TIRE_CAN_L: D101.2 (K2), J1.30, J1.34, JP1.2 (B), U21.6 (CANL)
/TIRE_CAN_OSC1: C81.1, U20.6 (OSC1), Y1.1
/TIRE_CAN_OSC2: C82.1, U20.5 (OSC2), Y1.3
/TIRE_CAN_RX: U20.2 (RXCAN), U21.4 (RXD)
/TIRE_CAN_SILENT: R71.2, U21.8 (S), U22.4 (Y)
/TIRE_CAN_TERM: JP1.1 (A), R70.2
/TIRE_CAN_TX: R69.2, U20.1 (TXCAN), U21.1 (TXD)
/TIRE_CAN_TX_ENABLE: R68.1, U20.9 (GPIO0_XSTBY), U22.2 (B)
/TWAI_RX: U1.5 (IO5), U100.4 (RXD)
/TWAI_TX: U1.4 (IO4), U100.1 (TXD)
/VCC_3V3: C11.1, U7.6 (VCC)
/VCC_PRE: C4.1, U5.6 (VCC)
/WHEEL_FRONT_CAPTURE: R118.2, U1.39 (IO1)
/WHEEL_FRONT_DIODE_OUT: D102.2 (K2), R112.1
/WHEEL_FRONT_FILTERED: C95.1, R112.2, R113.1, U26.2 (IN1-)
/WHEEL_FRONT_OUT: R116.1, R117.2, R118.1, U26.1 (OUT1)
/WHEEL_FRONT_PULLUP: D102.1 (A1), R111.2
/WHEEL_FRONT_PULLUP_MID: R110.2, R111.1
/WHEEL_FRONT_THRESHOLD: R114.2, R115.1, R116.2, U26.3 (IN1+)
/WHEEL_REAR_CAPTURE: R127.2, U1.38 (IO2)
/WHEEL_REAR_DIODE_OUT: D103.2 (K2), R121.1
/WHEEL_REAR_FILTERED: C96.1, R121.2, R122.1, U26.6 (IN2-)
/WHEEL_REAR_OUT: R125.1, R126.2, R127.1, U26.7 (OUT2)
/WHEEL_REAR_PULLUP: D103.1 (A1), R120.2
/WHEEL_REAR_PULLUP_MID: R119.2, R120.1
/WHEEL_REAR_THRESHOLD: R123.2, R124.1, R125.2, U26.5 (IN2+)

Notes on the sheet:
ADC
Sensor input dividers and buffers
Optional thermistor excitation - qualification pending
TIRE protected sensor power - validation pending
3V3 regulator (U7) and 3V3 bulk
FRONT protected sensor power - validation pending
Auxiliary input buffers - candidate
REAR protected sensor power - validation pending
Independent rail supervision - qualification pending
Rail diagnostics - qualification pending
Power entry and reverse protection
GNSS receiver and antenna feed
CAN transceiver
MCU
6V3 pre-regulator (U5)
5V reference, sensor and CAN supplies
IMU
Auxiliary power and diagnostic - qualification pending
Test points
microSD storage (owner decision 2026-10-21: eMMC dropped)
Pod connector
Dedicated tire CAN - power and validation pending
Hall input conditioning - qualification pending

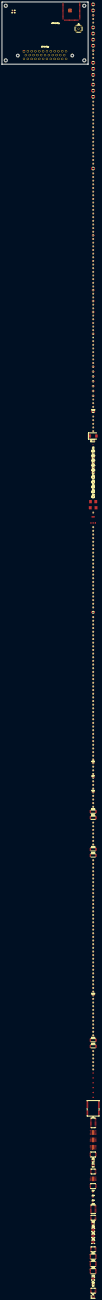
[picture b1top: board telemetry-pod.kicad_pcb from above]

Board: 4 copper layers, 90.0 x 65.0 mm, 313 parts (1 on the bottom side), 182 nets, no tracks yet.

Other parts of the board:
H1, H2, H3, H4: MountingHole; AgentEE_Mechanical_MountingHole_NPTH

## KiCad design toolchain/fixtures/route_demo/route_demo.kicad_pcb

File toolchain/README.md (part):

# fome-mc EDA toolchain

CLI-first, pinned tooling for the FOME-MC motorcycle ECU (this repo, `~/git/fome-mc`).
The Polygonus Universal 112 dual-WBO board
(`~/git/Polygonus-Universal-112`) is the electrical baseline and is checked read-only
alongside it.

Scope: tool installation and integration only. Native KiCad files stay
authoritative; nothing here edits, refills, upgrades or re-saves a design file.

PCB trace routing (KRT and Freerouting, `make route-*`) uses the standalone
[kicad-route](https://github.com/halbritt/kicad-route) tool, installed once per machine;
see [ROUTING.md](ROUTING.md). Unlike the pinned tools here, kicad-route and its backends
follow their latest upstream releases.

## Quick start

```bash
make bootstrap   # install/repair everything (uses sudo for apt), then doctor
make doctor      # verify versions, dependencies, libraries, capabilities, skills
make smoke       # integration checks on the RC fixture -> reports/toolchain/smoke/
make check       # ERC, DRC, netlist, exports, analysis on fome-mc (one snapshot)
make baseline    # read-only: committed HEAD of fome-mc + universal-112, and fome-mc's
                 # working tree -> reports/toolchain/baseline/
```

`toolchain/bootstrap.sh --no-apt` skips system packages (no sudo).

## What is installed (pins in `versions.toml`, `pyproject.toml`, `uv.lock`)

| Component | Version | Source / location |
|---|---|---|
| KiCad (`kicad-cli`, pcbnew bindings) | 10.0.7 stable | apt, `ppa:kicad/kicad-10.0-releases` (existing install) |
| KiCad stock symbols/footprints/templates | 10.0.7 | apt `kicad-symbols`, `kicad-footprints`, `kicad-templates` |
| ngspice (standalone CLI) | 42 (`42+ds-3build1`) | apt (Ubuntu noble) |
| KiBot | 1.9.1 (+ KiAuto 2.3.10) | `toolchain/.venv` via `uv.lock` |
| kicad-happy | v2.3.1 `06840467ad0f` | `toolchain/vendor/kicad-happy` (git, pinned commit) |
| Python | 3.12.3 (system interpreter, isolated venv) | `toolchain/.venv`: pytest 8.4.2, numpy 2.3.3, jsonschema 4.25.1, PyYAML 6.0.3, lxml 6.0.2 |
| PDF tools | poppler-utils 24.02.0, mupdf-tools 1.23.10, ghostscript 10.02.1 | apt |
| rsvg-convert | librsvg2-bin 2.58.0 | apt (KiBot `pcb_print` PDF) |

The venv is created from `/usr/bin/python3` and sees exactly three things from the
system: `pcbnew.py`, `_pcbnew.so` and `wx` (through `.venv/kicad-shim` and a `.pth`
file). KiBot needs KiCad's own bindings and the wxPython they were built against;
nothing else from system site-packages leaks in, and system Python is not modified.

KiBot runs with `-A` (no dependency auto-download). The stock 3D model library is
optional; `doctor` reports `UNSUPPORTED` when it is absent. The separate
[3D render workflow](#3d-board-renders) can use a persistent model cache.

## 3D board renders

`make render-3d` calls the installed `agent-ee render3d` command to render the
saved FOME board. It is separate from `make check`, `make export`, `make renders`
and `make smoke`; ordinary checks do not launch these expensive renders.

```sh
# First use: explicitly permit stock model downloads into a persistent cache:
make render-3d MODELS="$HOME/.cache/agent-ee/models" FETCH_MODELS=1
# Later runs can use the populated cache without downloads:
make render-3d
# Smaller preview using the same three native views:
make render-3d RENDER_WIDTH=800 RENDER_HEIGHT=600
# Inspect the images and model coverage, then publish the selected run:
make render-3d-publish RUN=build/runs/project/fome-mc/3d-renders-<stamp>
```

Install an agent-ee version with `render3d`, or select its launcher with
`AGENT_EE=/path/to/agent-ee/bin/agent-ee`. `MODELS` defaults to
`$HOME/.cache/agent-ee/models`; network model fetching requires `FETCH_MODELS=1`.
Populate that cache explicitly or select an existing model directory before an
offline run. A missing cache is an error; ordinary rendering does not download it.
`RENDER_WIDTH=4096`, `RENDER_HEIGHT=3072`, `RENDER_QUALITY=high`, `RENDER_JOBS=3`
and `RENDER_TIMEOUT=1200` set the defaults. The timeout is passed to agent-ee in
seconds. Native KiCad may produce dimensions slightly smaller than requested;
the manifest records the actual dimensions.

Each call creates a fresh `build/runs/project/fome-mc/3d-renders-<UTC stamp>/`
containing the native renderer's staged inputs, logs and `render-manifest.json`.
The adapter does not edit or refill the source board. Publication requires a
completed manifest with unchanged source, all three views with matching PNG dimensions and hashes,
and board/project hashes matching the current checkout. It replaces only
`fome-mc-3d-top.png`, `fome-mc-3d-bottom.png`, `fome-mc-3d-isometric.png` and
`render-manifest.json` in `docs/renders/3d/`. Invalid or partial runs leave the
published files untouched. Rerender after changing the source board or project.

Read `model_coverage` and the retained native logs before publishing. Stock
models cannot supply component bodies for footprints with no model reference
or unavailable custom models. A completed render is a visual preview and does
not establish mechanical clearance, ERC/DRC success or fabrication approval.

## Commands

The native check targets take `PROJECT=fome-mc|telemetry-pod|universal-112|fixture` (default `fome-mc`),
`FILL=asis|refill` (default `asis`) and `REV=<git revision>` (snapshot a committed
revision via `git archive` instead of the working tree; the run is labelled
`<project>@<rev>`).

| Target | Native command(s) |
|---|---|
| `erc` | `kicad-cli sch erc --format json --severity-all --units mm` |
| `drc` | `kicad-cli pcb drc --format json --severity-all --schematic-parity --units mm` |
| `netlist` | `kicad-cli sch export netlist --format kicadsexpr` → `connectivity.json` |
| `export` | DRC first, then `kicad-cli sch export pdf/svg/bom`, `kicad-cli pcb export pdf`, and `kibot -A -c toolchain/kibot/export.kibot.yaml` (Gerbers + job file, Excellon + report + map, positions, BOM CSV/HTML, schematic PDF, PCB print PDF) |
| `analyze` | kicad-happy `analyze_schematic.py` → `analyze_pcb.py --full --schematic schematic.json` → `cross_analysis.py` → `simulate_subcircuits.py --simulator ngspice` |
| `check` | all five steps on one snapshot |
| `renders` | `python3 scripts/render_docs.py` (regenerate 16 schematic SVGs/PDFs + 14 PCB SVGs/PDFs + composite renders) |
| `verify-io` | `python3 scripts/verify_io_map.py --project <PROJECT>` (default ECU audit or project-local I/O map and contracts; see below) |
| `fab-package [REV=HEAD]` | `python3 scripts/generate_fab_package.py --project <PROJECT>` (normalize Gerbers/drills and emit the project's `reports/toolchain/fab-manifest.json`) |
| `verify-fab-package [REV=HEAD]` | `python3 scripts/generate_fab_package.py --project <PROJECT> --verify` (verify `fab-manifest.json` SHA-256 parity and zero-diff reproducibility) |
| `simulate DECK=… [EXPECT=…]` | ngspice via a generated control script (below) |
| `smoke` | `pytest toolchain/tests` |
| `baseline` | `check` on the committed HEAD of fome-mc and universal-112, plus fome-mc's working tree (`fome-mc-worktree`); publishes reports |
| `doctor`, `bootstrap`, `skills` | environment check / install / regenerate agent skills |

Direct use: `python3 toolchain/eda.py --help`.

## Project I/O maps and fabrication packages

`make verify-io PROJECT=fome-mc` keeps the ECU audit, including its pin expectations,
firmware configuration in `~/git/fome-fw`, YAML connectors and sheet contracts.
`make verify-io PROJECT=telemetry-pod` reads `telemetry-pod/io-map.csv`, then
requires exactly `contracts/telemetry-pod.interface.json` at the repository root.
The committed contract is compiled by AGENTEE-188 from the pod map and its
explicit terminal bindings and indirect MCU paths. The pod map describes the Rev-3
source schematic named in `telemetry-pod/pinout-checks/source.json`, not the v9
pilot at the project root. The gate checks that schematic's pinned SHA-256 and
builds its native inventory from it. It requires `pinout-checks/generate.py --check`
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
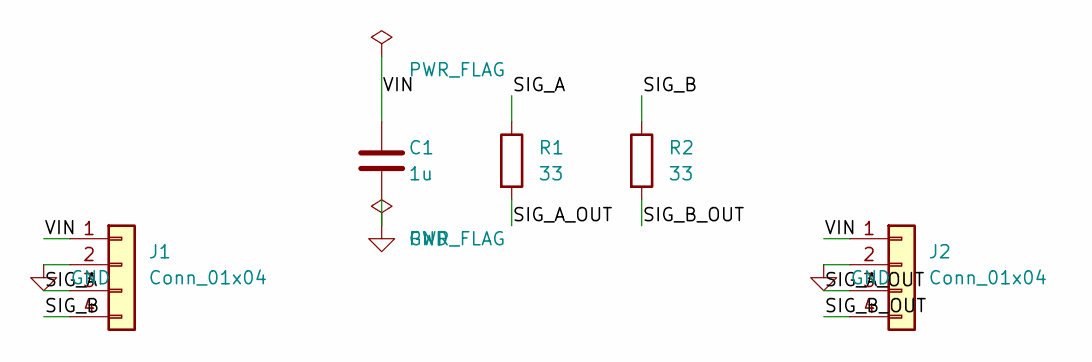
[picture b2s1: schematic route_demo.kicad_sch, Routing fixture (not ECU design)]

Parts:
C1: 1u; C_0805_2012Metric
J1, J2: Conn_01x04; PinHeader_1x04_P2.54mm_Vertical
R1, R2: 33; R_0805_2012Metric

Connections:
/SIG_A: J1.3, R1.1
/SIG_A_OUT: J2.3, R1.2
/SIG_B: J1.4, R2.1
/SIG_B_OUT: J2.4, R2.2
/VIN: C1.1, J1.1, J2.1
GND: C1.2, J1.2, J2.2

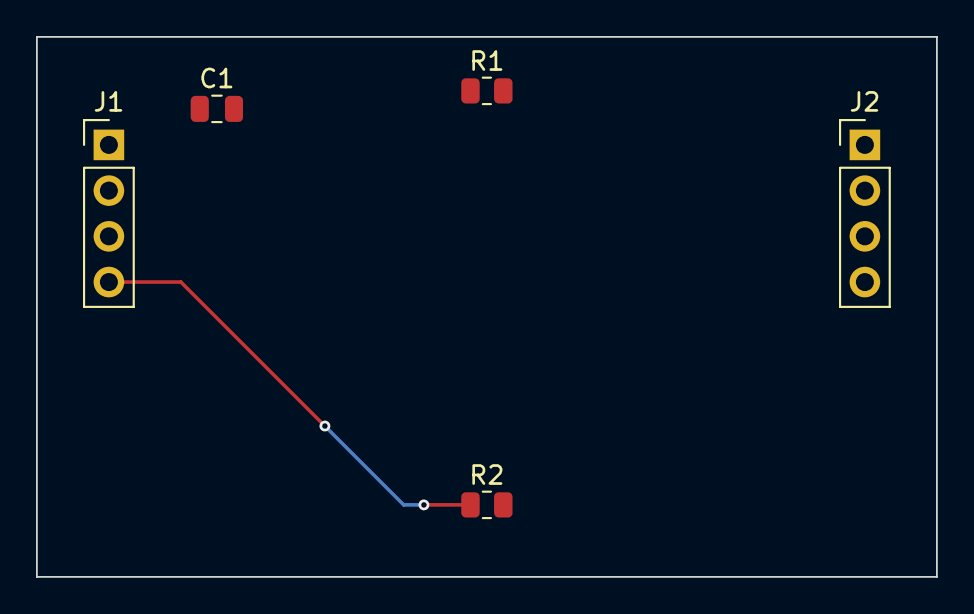
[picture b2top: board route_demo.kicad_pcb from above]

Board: 2 copper layers, 50.0 x 30.0 mm, 5 parts (0 on the bottom side), 6 nets.
